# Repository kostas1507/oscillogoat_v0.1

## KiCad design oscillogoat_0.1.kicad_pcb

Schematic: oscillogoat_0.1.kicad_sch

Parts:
C1, C10, C13, C14, C15, C16, C17, C18, C19, C20, C21: 100u; 1206_3216Metric; MANUFACTURER PART NUMBER GRM31CR61A107MEA8
C2, C3, C5, C6, C7, C8, C11, C55, C56, C57, C58, C59, C60, C62, C63, C64, C66, C67, C68, C69, C70, C76, C77, C78, C80, C81, C83, C84, C86, C102, C112, C125, C126, C127, C138, C139, C140, C147, C163, C164, C165, C171, C172, C173, C187, C188, C192, C194, C196, C201, C202, C1038_1, C1043_1, C1044_1, C1045_1, C1046_1, C1047_1, C1048_1, C1049_1, C1050_1, C1052_1, C1053_1, C1054_1, C1055_1, C1056_1, C1057_1: 1uF; 0402_1005Metric; VOLTAGE RATING 25V; MANUFACTURER PART NUMBER GRM155R61E105KA12D
C4, C74, C174, C178, C190, C1034_1, C1035_1: 100pF; 0402_1005Metric; VOLTAGE RATING 50V; MANUFACTURER PART NUMBER GCM1555C1H101FA16D
C9, C12, C71, C72, C73, C85, C93, C94, C95, C96, C106, C111, C114, C115, C116, C117, C119, C120, C121, C122, C130, C131, C133, C142, C143, C144, C145, C146, C148, C149, C150, C151, C152, C153, C156, C166, C167, C169, C170, C175, C179, C181, C182, C183, C184, C186, C189, C203, C1003_1, C1004_1, C1005_1, C1006_1, C1007_1, C1007_2, C1007_3, C1008_1, C1008_2, C1040_1: 10uF; 0603_1608Metric; VOLTAGE RATING 25V; MANUFACTURER PART NUMBER GRM188R61E106MA73D
C75, C99, C101, C104, C105, C128, C176, C177, C180, C191: 22uF; 0805_2012Metric; VOLTAGE RATING 25V; MANUFACTURER PART NUMBER GRM21BR61E226ME44L
C82, C123, C124, C129, C132, C185, C1032_1, C1033_1, C1041_1, C1042_1: 100nF; 0402_1005Metric; VOLTAGE RATING 16V; MANUFACTURER PART NUMBER GCM155R71C104KA55D
C100: 12pF; 0402_1005Metric; VOLTAGE RATING 50V; MANUFACTURER PART NUMBER CBR04C120F5GAC
C154, C155, C168, C195: 47uF; 0805_2012Metric; VOLTAGE RATING 6.3V; MANUFACTURER PART NUMBER CL21A476MQYNNNE
C193, C197, C198, C199, C200: 100nF; 0402_1005Metric
C1002_1: 68pF; 0402_1005Metric; VOLTAGE RATING 50V; MANUFACTURER PART NUMBER GCM1555C1H680FA16J
C1030_1: 1nF; 0603_1608Metric; VOLTAGE RATING 100V; MANUFACTURER PART NUMBER GCM1885C2A102FA16D
F1, F2, F3, F4, F5, F6, F7, F8, F9, F10, F11: 120@100MHZ; 0402_1005Metric; MANUFACTURER PART NUMBER BLM15PX121SN1D
FB1001_1: 120@100MHZ; 0402_1005Metric; MANUFACTURER PART NUMBER BLM15PX121SN1D
IC1: XC7A12T-1CPG238C; BGA238C50P19X19_1000X1000X138; Mouser Part Number 217-XC7A12T-1CPG238C
IC2: FT601Q-B-T; QFN40P900X900X100-77N-D; Mouser Part Number 895-FT601Q-B-T
IC5: ADC09DJ800AAV; BGA144C80P12X12_1000X1000X194; Mouser Part Number 595-ADC09DJ800AAV
J1: 10137062-00021LF; 1013706200021LF; Manufacturer_Part_Number 10137062-00021LF
J5, J6: 2.54mm 6 Pin TH; GEN_2.54MM_6_PIN_TH_RA; MANUFACTURER PART NUMBER 61300611021
J1002_1: BNC; MOL_0731000105; MANUFACTURER PART NUMBER 73100-0105
L1, L2, L3, L5, L6: 1uH; 1210_3225Metric; MANUFACTURER PART NUMBER SRP3212-1R0M
Q1, Q2: DMN62D0UW; GEN_SOT_323; MANUFACTURER PART NUMBER DMN62D0UW-7
R1, R66, R67, R68, R72, R111, R117, R118, R121, R124, R131, R132, R1033_1, R1044_1: 10K; 0402_1005Metric; TOLERANCE 1%; MANUFACTURER PART NUMBER ERJ-2RKF1002X
R3: DNP; 0402_1005Metric; TOLERANCE 1%
R4, R6: DNP (place for LED); 0402_1005Metric; TOLERANCE 1%
R5: DNP (place for LED current limiter); 0402_1005Metric; TOLERANCE 1%
R7: 0; 0402_1005Metric; TOLERANCE 1%
R9, R10, R11, R12, R69, R99, R104, R112, R119, R136, R137, R138, R139, R140: 4.7K; 0402_1005Metric; TOLERANCE 1%; MANUFACTURER PART NUMBER ERJ-2RKF4701X
R13: 10K; GEN_R_2ARRAY_0606; TOLERANCE 1%; MANUFACTURER PART NUMBER ACASN1002S1002P1ATF1002X
R14, R57, R97, R98, R103, R116, R120, R123, R134: 0R01; 0603_1608Metric; TOLERANCE 1%; MANUFACTURER PART NUMBER RL0816T-R010-F
R15: 1K6R; 0402_1005Metric; TOLERANCE 1%
R16: 4K7R; 0402_1005Metric; TOLERANCE 1%
R17, R18: 10KR; 0402_1005Metric; TOLERANCE 1%
R52_1, R97_1: 0; 0402_1005Metric; MANUFACTURER PART NUMBER RC0402JR-070RL
R55, R96, R1041_1, R1042_1, R1047_1: 90.9k; 0402_1005Metric; TOLERANCE 1%; MANUFACTURER PART NUMBER RC0402FR-0790K9L
R56, R100, R105, R122: 20k; 0402_1005Metric; TOLERANCE 1%; MANUFACTURER PART NUMBER RC0402FR-0720KL
R70, R73: 5.1K; 0402_1005Metric; TOLERANCE 1%
R71: 3.75k; 0402_1005Metric; TOLERANCE 1%
R90, R106: 0.1; 0402_1005Metric; TOLERANCE 1%; MANUFACTURER PART NUMBER ERJ-2BSFR10X
R93, R109: 280K; 0402_1005Metric; TOLERANCE 1%; MANUFACTURER PART NUMBER AC0402FR-07280KL
R102: 3.4k; 0402_1005Metric; TOLERANCE 1%
R107, R143: 100; 0402_1005Metric; TOLERANCE 1%; MANUFACTURER PART NUMBER RC0402FR-07100RL
R110, R1036_1: 35.7k; 0402_1005Metric; TOLERANCE 1%; MANUFACTURER PART NUMBER RC0402FR-0735K7L
R113: 12.8k; 0402_1005Metric; TOLERANCE 1%
R125, R1045_1, R1046_1: 1K; 0402_1005Metric; TOLERANCE 1%; MANUFACTURER PART NUMBER RC0402FR-071KL
R127, R1043_1: 2K; 0402_1005Metric; TOLERANCE 1%; MANUFACTURER PART NUMBER RC0402FR-072KL
R141: 0R1; 0402_1005Metric; TOLERANCE 1%
R1003_1, R1038_1: 10M; 0603_1608Metric; TOLERANCE 1%; MANUFACTURER PART NUMBER RK73H1JTTD1005F
R1022_1, R1035_1: 30; 0603_1608Metric; TOLERANCE 1%; MANUFACTURER PART NUMBER SG73P1JTTD30R0F
R1037_1: 0; 0402_1005Metric; TOLERANCE 1%; MANUFACTURER PART NUMBER RC0402JR-070RL
R1039_1: 909k; 0402_1005Metric; TOLERANCE 1%; MANUFACTURER PART NUMBER RC0402FR-07909KL
R1048_1: DNP; 0402_1005Metric; TOLERANCE 1%; not fitted
R1049_1: 2K TRIMPOT; BOU_3mm_POT; TOLERANCE 1%; MANUFACTURER PART NUMBER TC33X-2-202E
S1: 416131160803
TP6, TP7, TP8, TP9, TP21, TP22, TP28, TP32, TP33, TP34, TP36, TP37, TP38, TP40, TP41, TP42, TP43, TP44, TP45, TP46, TP47, TP48, TP49, TP50, TP51, TP52, TP53, TP54, TP55, TP56, TP58, TP59, TP60, TP61, TP62, TP63, TP64, TP65, TP66, TP67, TP69, TP70, TP71, TP72, TP75, TP76, TP77, TP78, TP79, TP80, TP81, TP1017_1: PCB; GEN_TP_PCB
U2: MCP4452-104E; MC_TSSOP14; MANUFACTURER PART NUMBER MCP4452-104E
U3: MCP4728; MC_MSOP10_UN; MANUFACTURER PART NUMBER MCP4728T-E/UN
U4: REF2025; GEN_SOT23_5_950_2900X1600X1450; MANUFACTURER PART NUMBER REF2025AIDDCR
U5, U1011_1: OPA140AIDBVR; GEN_SOT23_5_950_2900X1600X1450; MANUFACTURER PART NUMBER OPA140AIDBVR
U8, U20, U21, U24: TPS62A02; TI_SOT563_DRL0006A; MANUFACTURER PART NUMBER TPS62A02DRLR
U13: LM27761; TI_WSON8_DSG0008A; MANUFACTURER PART NUMBER LM27761DSGR
U14, U15, U18, U22: TPS7A9101; TI_WSON10_DSK0010A; MANUFACTURER PART NUMBER TPS7A9101DSKR
U16: TPS7A2033; GEN_SOT23_5_950_2900X1600X1450; MANUFACTURER PART NUMBER TPS7A2033PDBVR
U17: TPS61023; TI_SOT563_DRL0006A; MANUFACTURER PART NUMBER TPS61023DRLT
U19: MX25L6433FZNI-08G; MX_WSON8; MANUFACTURER PART NUMBER MX25L6433FZNI-08G-TR
U1008_1: LMH6518; TI_WQFN_RGH0016A; MANUFACTURER PART NUMBER LMH6518SQX/NOPB
U1009_1: BUF802; TI_VQFN_RGT0016C; MANUFACTURER PART NUMBER BUF802IRGTR
Y1: ASEMPLV-100.000MHZ-LR-T; XTAL_ASEMPLV-100.000MHZ-LR-T; PARTREV 12.6.2018
Y2: 830107284409; Mouser Part Number 710-830107284409

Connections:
+1V0: C163.1, C164.1, C166.2, C167.2, C195.2, C196.1, F7.2, IC1.G10 (VCCINT_1), IC1.H10 (VCCINT_2), IC1.J10 (VCCINT_3), IC1.L10 (VCCINT_4), IC1.M10 (VCCINT_5), IC1.M11 (VCCBRAM_1), IC1.N10 (VCCINT_6), IC1.N11 (VCCBRAM_2), R116.2, TP66.1 (1_1)
+1V0_MGT: C17.1, C81.1, C83.1, F7.1, IC1.C1 (MGTAVCC_1), IC1.E1 (MGTAVCC_2), IC1.G9 (MGTAVCC_3), IC1.H9 (MGTAVCC_4)
+1V1_ACQ: C105.2, C133.2, C146.2, C149.2, C150.2, C152.2, F1.2, F2.2, F3.2, IC5.D8 (PLL_EN), R112.2, TP45.1 (1_1), U18.1 (OUT), U18.2 (OUT)
+1V2_MGT: C18.1, C84.1, C86.1, C183.2, C184.2, F8.1, F8.2, IC1.B1 (MGTAVTT_1), IC1.C5 (MGTAVTT_2), IC1.E2 (MGTAVTT_3), IC1.G7 (MGTAVTT_4), R125.1, R143.1, TP50.1 (1_1), U22.1 (OUT), U22.2 (OUT)
+1V8: C165.1, C168.2, C169.2, C170.2, C171.1, C172.1, C173.1, C186.2, C203.2, IC1.B19 (VCCO_15_1), IC1.C9 (VCCBATT_0), IC1.C14 (VCCO_15_2), IC1.C18 (VCCO_15_3), IC1.G13 (VCCO_15_4), IC1.H13 (VCCAUX_1), IC1.J13 (VCCAUX_2), R120.2, R123.1, R141.1, TP51.1 (1_1), TP64.1 (1_1)
+1V9_ACQ: C104.2, C117.2, C144.2, C145.2, C148.2, C151.2, F4.2, F5.2, F6.2, J6.1, R99.2, TP33.1 (1_1), U14.1 (OUT), U14.2 (OUT)
+2V2_AQ: R97.1, R134.2, TP36.1 (1_1), TP72.1 (1_1)
+2V5: R103.1, TP42.1 (1_1)
+3V3: C129.2, C138.1, C139.1, C140.1, C142.2, C143.2, C147.1, C154.2, C155.2, C156.2, C187.1, C188.1, C192.1, C201.1, C202.1, IC1.G12 (VCCO_0_1), IC1.K12 (VCCO_14_1), IC1.K13 (VCCO_14_2), IC1.L12 (VCCO_14_3), IC1.L13 (VCCO_14_4), IC1.M12 (VCCO_14_5), IC1.M13 (VCCO_14_6), IC1.N13 (VCCO_14_7), IC1.U12 (CFGBVS_0), IC1.V11 (VCCO_0_2), IC2.14 (VCCIO_1), IC2.20 (VCC33_1), IC2.24 (VCC33_2), IC2.28 (VDDA), IC2.38 (VCC33_3), IC2.49 (VCCIO_2), IC2.59 (VCCIO_3), IC2.68 (VCCIO_4), J5.6, R18.1, R57.2, R66.1, R67.2, R68.1, R136.2, R137.2, R138.2, R139.2, R140.2, TP70.1 (1_1), U19.8 (VCC), Y1.1 (TRI-STATE), Y1.6 (VDD)
+3V3_PGA: C76.1, C126.1, C1043_1.1, Q1.2 (G), Q2.2 (G), R9.2, R10.2, R1033_1.1, U16.5 (OUT), U1008_1.12 (VDD)
+5V: C2.1, C3.1, C5.1, C8.1, C85.2, C94.2, C95.2, C96.2, C121.2, C122.2, C1007_3.1, C1040_1.2, F9.1, F11.2, R11.2, R12.2, R100.2, R106.1, TP40.1 (1_1), U2.12 (VDD), U3.1 (VDD), U4.3 (EN), U4.4 (VIN), U5.5 (V+), U15.1 (OUT), U15.2 (OUT)
+5V3: C100.2, C101.2, C102.1, C128.2, R90.1, R98.1, R109.2, TP37.1 (1_1), TP41.1 (1_1), U17.6 (VOUT)
+5V_BUF: C21.1, C1004_1.2, C1006_1.2, C1008_1.2, C1044_1.1, C1045_1.1, C1046_1.1, C1047_1.1, C1048_1.1, C1049_1.1, C1050_1.1, F11.1, U1009_1.1 (Vs+), U1009_1.12 (Vso+), U1009_1.15 (CLH), U1011_1.5 (V+)
+5V_PGA: C19.1, C1008_2.2, C1038_1.1, F9.2, U1008_1.3 (VCC), U1008_1.4 (VCC)
+VBIAS: C6.1, C1033_1.2, R13.2, R1045_1.1, R1046_1.1, TP8.1 (1_1), U4.5 (VREF)
+VUSB: C9.2, C12.2, C71.2, C72.2, C73.2, C175.2, C179.2, C189.2, J1.A4 (VBUS_1), J1.A9 (VBUS_2), J1.B4 (VBUS_3), J1.B9 (VBUS_4), R1.2, R14.1, R16.2, R117.2, R121.2, R131.2, TP21.1 (1_1), U8.3 (VIN), U20.3 (VIN), U21.3 (VIN), U24.3 (VIN)
-5V: C11.2, C93.1, C106.2, C1007_2.1, F10.1, R93.2, U5.2 (V-), U13.4 (VOUT)
-5V_BUF: C20.1, C1003_1.1, C1005_1.1, C1007_1.1, C1052_1.2, C1053_1.2, C1054_1.2, C1055_1.2, C1056_1.2, C1057_1.2, F10.2, R1036_1.2, U1009_1.5 (Vs-), U1009_1.6 (Aux_Bias), U1009_1.8 (Vs-), U1009_1.10 (Vso-), U1011_1.2 (V-)
-VBIAS: C82.2, C1032_1.2, R107.1, R1042_1.1, TP9.1 (1_1)
/1V9_AQ_PG: U14.5 (PG), U18.7 (EN)
/+1V0_R: C174.2, C176.2, C177.2, L2.2, R69.2, R116.1, R118.2, TP65.1 (1_1)
/+1V8_R: C178.2, C180.2, L3.2, R120.1, R122.2, TP63.1 (1_1)
/+1V8_R_LDO: C181.2, C182.2, R123.2, TP49.1 (1_1), U22.6 (SS_CTRL), U22.9 (IN), U22.10 (IN)
/+2V5_R: C190.2, C191.2, L6.2, R132.2, R134.1, TP71.1 (1_1)
/+2V5_R_ACQ: C115.2, C116.2, C130.2, C131.2, R97.2, R103.2, TP32.1 (1_1), TP44.1 (1_1), U14.6 (SS_CTRL), U14.9 (IN), U14.10 (IN), U18.6 (SS_CTRL), U18.9 (IN), U18.10 (IN)
/+3V3_R: C74.2, C75.2, L5.2, R55.1, R57.1, TP69.1 (1_1)
/+5V3_R_CP: C111.2, R90.2, TP28.1 (1_1), U13.1 (VIN)
/+5V3_R_LDO: C119.2, C120.2, R98.2, TP34.1 (1_1), U15.9 (IN), U15.10 (IN)
/+5V_R_PGA: C125.1, R106.2, TP38.1 (1_1), U16.1 (IN), U16.3 (EN)
/+VUSB_R: C99.2, C127.1, L1.1, R14.2, R72.2, TP22.1 (1_1), U17.3 (VIN)
/ADC_DEVCLK_N: IC5.G1 (CLK-), Y1.5 (~OUTPUT)
/ADC_DEVCLK_P: IC5.F1 (CLK+), Y1.4 (OUTPUT)
/ADC_INA+: IC5.A2 (INA+)
/ADC_INA-: IC5.A3 (INA-)
/ADC_JESD_0_N: IC1.A4 (MGTPRXN0_216), IC5.K12 (D0-)
/ADC_JESD_0_P: IC1.B4 (MGTPRXP0_216), IC5.J12 (D0+)
/ADC_JESD_1_N: IC1.A6 (MGTPRXN1_216), IC5.H12 (D1-)
/ADC_JESD_1_P: IC1.B6 (MGTPRXP1_216), IC5.G12 (D1+)
/ADC_SPI_CLK: IC1.A17 (IO_L6N_T0_VREF_15), IC5.F8 (SCLK), J6.2
/ADC_SPI_SCS: IC1.A15 (IO_L10N_T1_AD4N_15), IC5.E8 (~SCS), J6.3
/ADC_SPI_SDI: IC1.A14 (IO_L10P_T1_AD4P_15), IC5.G8 (SDI), J6.4
/ADC_SPI_SDO: IC1.A16 (IO_L11N_T1_SRCC_AD12N_15), IC5.G9 (SDO), J6.5
/ATTEN_OUT: R1022_1.1, R1035_1.1, R1039_1.1
/ATTEN_OUT_R: C1030_1.2, R1035_1.2
/BE_0: IC1.R17 (IO_L17N_T2_A13_D29_14), IC2.4 (BE_0)
/BE_1: IC1.T17 (IO_L18P_T2_A12_D28_14), IC2.5 (BE_1)
/BE_2: IC1.P17 (IO_L17P_T2_A14_D30_14), IC2.6 (BE_2)
/BE_3: IC1.N17 (IO_L14P_T2_SRCC_14), IC2.7 (BE_3)
/BUF_IN: C1030_1.1, R1038_1.2, U1009_1.2 (IN)
/BUF_IN_AUX: C1034_1.2, R1043_1.1, U1009_1.4 (IN_Aux)
/BUF_IN_BIAS: R1038_1.1, U1009_1.3 (IN_Bias)
/BUF_OUT: R1037_1.1, R1041_1.1, U1009_1.11 (OUT)
/BUF_OUT_R: R1037_1.2, U1008_1.6 (IN_P)
/BUF_R_BIAS: R1036_1.1, U1009_1.7 (R_Bias)
/DC_FB: C1002_1.2, C1035_1.2, R1041_1.2, R1042_1.2, R1044_1.1, U1011_1.4 (-)
/DC_FB_TRIM: R1044_1.2, R1048_1.2, R1049_1.1, R1049_1.2
/DN: IC2.25 (DM), J1.A7 (DN1), J1.B7 (DN2)
/DONE: IC1.U11 (DONE_0), R3.2
/DP: IC2.23 (DP), J1.A6 (DP1), J1.B6 (DP2)
/FE_EN: R111.1, U13.6 (EN), U15.7 (EN)
/FE_PG: U15.5 (PG)
/FPGA_EN: R117.1, TP81.1 (1_1), U20.4 (EN)
/FTDI_XI: C199.2, IC2.21 (XI), Y2.3 (CRYSTAL_2)
/FTDI_XO: C200.1, IC2.22 (XO), Y2.1 (CRYSTAL_1)
/M0: IC1.V13 (M0_0), R140.1, S1.A3
/M1: IC1.W13 (M1_0), R139.1, S1.A2
/M2: IC1.U13 (M2_0), R138.1, S1.A1
/OE_N: IC1.U17 (IO_L19P_T3_A10_D26_14), IC2.13 (OE_N)
/OPA_OUT: C1002_1.1, C1035_1.1, R1043_1.2, U1011_1.1 (OUT)
/OUT_N: R97_1.2
/OUT_P: R52_1.2
/OUT_R_N: R97_1.1, U1008_1.14 (OUT_N)
/OUT_R_P: R52_1.1, U1008_1.15 (OUT_P)
/PGA_BIAS: C1042_1.2, FB1001_1.2, R1045_1.2, R1046_1.2, TP1017_1.1 (1_1), U1008_1.7 (IN_N)
/PGA_CSn: R1033_1.2, U1008_1.9 (CSn)
/PGA_SCLK: U1008_1.11 (SCLK)
/PGA_SDIO: U1008_1.10 (SDIO)
/PG_1V0: R121.1, TP79.1 (1_1), U20.6 (PG), U21.4 (EN)
/PG_1V8: R1.1, R131.1, TP80.1 (1_1), U8.4 (EN), U21.6 (PG), U22.7 (EN), U24.4 (EN)
/QSPI_CLK: IC1.C11 (CCLK_0), TP43.1 (1_1), U19.6 (SCLK)
/QSPI_CS: IC1.G19 (IO_L6P_T0_FCS_B_14), R67.1, TP53.1 (1_1), U19.1 (CS#)
/QSPI_DQ0: IC1.D18 (IO_L1P_T0_D00_MOSI_14), TP47.1 (1_1), U19.5 (SI/SIO0)
/QSPI_DQ1: IC1.D19 (IO_L1N_T0_D01_DIN_14), TP46.1 (1_1), U19.2 (SO/SIO1)
/QSPI_DQ2: IC1.E19 (IO_L2P_T0_D02_14), R66.2, TP48.1 (1_1), U19.3 (WP#/SIO2)
/QSPI_DQ3: IC1.F19 (IO_L2N_T0_D03_14), R68.2, TP52.1 (1_1), U19.7 (HOLD#/SIO3)
/RD_N: IC1.U16 (IO_L22N_T3_A04_D20_14), IC2.12 (RD_N)
/RXF_N: IC1.V16 (IO_L21P_T3_DQS_14), IC2.9 (RXF_N)
/SIWU_N: IC1.V14 (IO_L23P_T3_A03_D19_14), IC2.10 (SIWU_N)
/SSRXN: IC2.34 (RIDN), J1.A10 (SSRXN2)
/SSRXP: IC2.35 (RIDP), J1.A11 (SSRXP2)
/SSTXN: C193.1, J1.A3 (SSTXN1)
/SSTXP: C197.1, J1.A2 (SSTXP1)
/TCK: IC1.C8 (TCK_0), J5.4, TP77.1 (1_1)
/TDI: IC1.W11 (TDI_0), J5.2, TP75.1 (1_1)
/TDO: IC1.V10 (TDO_0), J5.3, TP76.1 (1_1)
/TMS: IC1.W10 (TMS_0), J5.1, TP78.1 (1_1)
/TRIM_1: C1041_1.2, FB1001_1.1, U2.14 (P2W)
/TRIM_2: U2.9 (P0W)
/TRIM_3: U2.8 (P1W)
/TRIM_4: U2.1 (P3W)
/TRIM_SCL: Q1.3 (S), R9.1, TP59.1 (1_1)
/TRIM_SCL_5V: Q1.1 (D), R11.1, TP6.1 (1_1), U2.4 (SCL), U3.2 (SCL)
/TRIM_SDA: Q2.3 (S), R10.1, TP60.1 (1_1)
/TRIM_SDA_5V: Q2.1 (D), R12.1, TP7.1 (1_1), U2.5 (SDA), U3.3 (SDA)
/TXE_N: IC1.U15 (IO_L22P_T3_A05_D21_14), IC2.8 (TXE_N)
/U5-: C4.1, R13.1, R13.3, U5.4 (-)
/VCM: U1008_1.13 (VCM)
/VOUT1: U2.13 (P2B), U3.6 (VOUTA)
/VOUT2: U2.10 (P0B), U3.7 (VOUTB)
/VOUT3: U2.7 (P1B), U3.8 (VOUTC)
/VOUT4: U2.2 (P3B), U3.9 (VOUTD)
/WR_N: IC1.U14 (IO_25_14), IC2.11 (WR_N)
/p0: IC1.G17 (IO_L5N_T0_D07_14), IC2.40 (DATA_0)
/p1: IC1.F17 (IO_L5P_T0_D06_14), IC2.41 (DATA_1)
/p2: IC1.E17 (IO_L3P_T0_DQS_PUDC_B_14), IC2.42 (DATA_2)
/p3: IC1.D17 (IO_0_14), IC2.43 (DATA_3)
/p4: IC1.M17 (IO_L10P_T1_D14_14), IC2.44 (DATA_4)
/p5: IC1.L17 (IO_L12N_T1_MRCC_14), IC2.45 (DATA_5)
/p6: IC1.K17 (IO_L12P_T1_MRCC_14), IC2.46 (DATA_6)
/p7: IC1.J17 (IO_L7N_T1_D10_14), IC2.47 (DATA_7)
/p8: IC1.H17 (IO_L7P_T1_D09_14), IC2.50 (DATA_8)
/p9: IC1.E18 (IO_L3N_T0_DQS_EMCCLK_14), IC2.51 (DATA_9)
/p10: IC1.G18 (IO_L4P_T0_D04_14), IC2.52 (DATA_10)
/p11: IC1.H18 (IO_L4N_T0_D05_14), IC2.53 (DATA_11)
/p12: IC1.K18 (IO_L11P_T1_SRCC_14), IC2.54 (DATA_12)
/p13: IC1.H19 (IO_L6N_T0_D08_VREF_14), IC2.55 (DATA_13)
/p14: IC1.J19 (IO_L8P_T1_D11_14), IC2.56 (DATA_14)
/p15: IC1.K19 (IO_L8N_T1_D12_14), IC2.57 (DATA_15)
/p16: IC1.L18 (IO_L11N_T1_SRCC_14), IC2.60 (DATA_16)
/p17: IC1.N18 (IO_L10N_T1_D15_14), IC2.61 (DATA_17)
/p18: IC1.P18 (IO_L14N_T2_SRCC_14), IC2.62 (DATA_18)
/p19: IC1.T18 (IO_L18N_T2_A11_D27_14), IC2.63 (DATA_19)
/p20: IC1.M19 (IO_L9N_T1_DQS_D13_14), IC2.64 (DATA_20)
/p21: IC1.N19 (IO_L13P_T2_MRCC_14), IC2.65 (DATA_21)
/p22: IC1.P19 (IO_L13N_T2_MRCC_14), IC2.66 (DATA_22)
/p23: IC1.R19 (IO_L15P_T2_DQS_RDWR_B_14), IC2.67 (DATA_23)
/p24: IC1.T19 (IO_L15N_T2_DQS_DOUT_CSO_B_14), IC2.69 (DATA_24)
/p25: IC1.U19 (IO_L16P_T2_CSI_B_14), IC2.70 (DATA_25)
/p26: IC1.V19 (IO_L16N_T2_A15_D31_14), IC2.71 (DATA_26)
/p27: IC1.W18 (IO_L20N_T3_A07_D23_14), IC2.72 (DATA_27)
/p28: IC1.W17 (IO_L20P_T3_A08_D24_14), IC2.73 (DATA_28)
/p29: IC1.W16 (IO_L24N_T3_A00_D16_14), IC2.74 (DATA_29)
/p30: IC1.W15 (IO_L24P_T3_A01_D17_14), IC2.75 (DATA_30)
/p31: IC2.76 (DATA_31), R7.1
/p31_FPGA: IC1.W14 (IO_L23N_T3_A02_D18_14), R5.2, R7.2
/p_CLK: IC1.L19 (IO_L9P_T1_DQS_14), IC2.58 (CLK)
GND: C1.2, C2.2, C3.2, C5.2, C6.2, C7.2, C8.2, C9.1, C10.2, C11.1, C12.1, C13.2, C14.2, C15.2, C16.2, C17.2, C18.2, C19.2, C20.2, C21.2, C55.2, C56.2, C57.2, C58.2, C59.2, C60.2, C62.2, C63.2, C64.2, C66.2, C67.2, C68.2, C69.2, C70.2, C71.1, C72.1, C73.1, C75.1, C76.2, C77.2, C78.2, C80.2, C81.2, C82.1, C83.2, C84.2, C85.1, C86.2, C93.2, C94.1, C95.1, C96.1, C99.1, C101.1, C102.2, C104.1, C105.1, C106.1, C111.1, C114.1, C115.1, C116.1, C117.1, C119.1, C120.1, C121.1, C122.1, C123.1, C124.1, C125.2, C126.2, C127.2, C128.1, C129.1, C130.1, C131.1, C132.1, C133.1, C138.2, C139.2, C140.2, C142.1, C143.1, C144.1, C145.1, C146.1, C147.2, C148.1, C149.1, C150.1, C151.1, C152.1, C153.1, C154.1, C155.1, C156.1, C163.2, C164.2, C165.2, C166.1, C167.1, C168.1, C169.1, C170.1, C171.2, C172.2, C173.2, C175.1, C176.1, C177.1, C179.1, C180.1, C181.1, C182.1, C183.1, C184.1, C185.1, C186.1, C187.2, C188.2, C189.1, C191.1, C192.2, C194.2, C195.1, C196.2, C198.1, C199.1, C200.2, C201.2, C202.2, C203.1, C1003_1.2, C1004_1.1, C1005_1.2, C1006_1.1, C1007_1.2, C1007_2.2, C1007_3.2, C1008_1.1, C1008_2.1, C1032_1.1, C1033_1.1, C1034_1.1, C1038_1.2, C1040_1.1, C1041_1.1, C1042_1.1, C1043_1.2, C1044_1.2, C1045_1.2, C1046_1.2, C1047_1.2, C1048_1.2, C1049_1.2, C1050_1.2, C1052_1.1, C1053_1.1, C1054_1.1, C1055_1.1, C1056_1.1, C1057_1.1, IC1.A1 (GND_1), IC1.A3 (GND_2), IC1.A5 (GND_3), IC1.A7 (GND_4), IC1.A9 (GND_5), IC1.A11 (DXP_0), IC1.A12 (VP_0), IC1.A13 (VREFN_0), IC1.A19 (GND_6), IC1.B3 (GND_7), IC1.B5 (GND_8), IC1.B7 (GND_9), IC1.B9 (GND_10), IC1.B11 (DXN_0), IC1.B12 (VREFP_0), IC1.B13 (VN_0), IC1.B14 (GND_11), IC1.C2 (GND_12), IC1.C3 (GND_13), IC1.C4 (GND_14), IC1.C6 (GND_15), IC1.C10 (GND_16), IC1.C12 (GNDADC_0), IC1.C19 (GND_17), IC1.D3 (GND_18), IC1.E3 (GND_19), IC1.F1 (GND_20), IC1.F2 (GND_21), IC1.F3 (GND_22), IC1.F18 (GND_23), IC1.G8 (GND_24), IC1.G11 (GND_25), IC1.H7 (GND_26), IC1.H8 (GND_27), IC1.H11 (GND_28), IC1.H12 (GND_29), IC1.J2 (GND_30), IC1.J7 (VCCO_34_1), IC1.J8 (GND_31), IC1.J9 (GND_32), IC1.J11 (GND_33), IC1.J12 (GND_34), IC1.J18 (GND_35), IC1.K7 (VCCO_34_2), IC1.K8 (GND_36), IC1.L7 (VCCO_34_3), IC1.L8 (GND_37), IC1.L9 (GND_38), IC1.L11 (GND_39), IC1.M2 (GND_40), IC1.M7 (VCCO_34_4), IC1.M8 (VCCO_34_5), IC1.M9 (GND_41), IC1.M18 (GND_42), IC1.N7 (VCCO_34_6), IC1.N8 (VCCO_34_7), IC1.N9 (GND_43), IC1.N12 (GND_44), IC1.R2 (GND_45), IC1.R18 (GND_46), IC1.V2 (GND_47), IC1.V5 (GND_48), IC1.V8 (GND_49), IC1.V12 (GND_50), IC1.V15 (GND_51), IC1.V18 (GND_52), IC1.W1 (GND_53), IC1.W19 (GND_54), IC2.1 (GND_1), IC2.26 (GND_2), IC2.29 (GND_3), IC2.36 (GND_4), IC2.77 (THERMAL_PAD), IC5.A1 (AGND_1), IC5.A4 (AGND_2), IC5.A5 (AGND_3), IC5.A8 (AGND_4), IC5.A11 (DGND_1), IC5.A12 (DGND_2), IC5.B1 (AGND_5), IC5.B2 (AGND_6), IC5.B3 (AGND_7), IC5.B4 (AGND_8), IC5.B5 (AGND_9), IC5.B6 (AGND_10), IC5.B7 (AGND_11), IC5.B8 (AGND_12), IC5.B11 (DGND_3), IC5.B12 (DGND_4), IC5.C2 (AGND_13), IC5.C4 (~SYNCSE), IC5.C5 (AGND_14), IC5.C6 (AGND_15), IC5.C7 (CLKCFG0), IC5.C8 (PLLREF_SE), IC5.C10 (DGND_5), IC5.D2 (AGND_16), IC5.D3 (AGND_17), IC5.D7 (CLKCFG1), IC5.E1 (AGND_18), IC5.E2 (AGND_19), IC5.E4 (AGND_20), IC5.E7 (AGND_21), IC5.F2 (SE_CLK), IC5.F4 (AGND_22), IC5.F7 (AGND_23), IC5.F10 (DGND_6), IC5.G2 (SE_GND), IC5.G4 (AGND_24), IC5.G7 (AGND_25), IC5.G10 (DGND_7), IC5.H1 (AGND_26), IC5.H2 (AGND_27), IC5.H4 (AGND_28), IC5.H7 (AGND_29), IC5.J2 (AGND_30), IC5.J3 (PGND_1), IC5.K2 (AGND_31), IC5.K5 (PGND_2), IC5.K10 (DGND_8), IC5.L1 (AGND_32), IC5.L2 (AGND_33), IC5.L3 (AGND_34), IC5.L4 (AGND_35), IC5.L5 (AGND_36), IC5.L6 (AGND_37), IC5.L7 (AGND_38), IC5.L8 (AGND_39), IC5.L9 (DGND_9), IC5.L11 (DGND_10), IC5.L12 (DGND_11), IC5.M1 (AGND_40), IC5.M4 (AGND_41), IC5.M5 (AGND_42), IC5.M8 (AGND_43), IC5.M9 (PD), IC5.M11 (DGND_12), IC5.M12 (DGND_13), J1.A1 (GND_1), J1.A12 (GND_2), J1.B1 (GND_3), J1.B12 (GND_4), J1.MH3 (MH4), J1.MH4 (MH1), J1.MH5 (MH3), J1.MH6 (MH2), J5.5, J6.6, J1002_1.2 (SHIELD), R4.1, R6.1, R15.1, R17.1, R56.1, R70.1, R71.1, R73.2, R96.1, R102.1, R104.1, R105.1, R110.2, R111.2, R113.1, R119.2, R124.1, R127.2, R1003_1.2, R1047_1.2, R1048_1.1, R1049_1.3, S1.1, S1.2, S1.3, U2.3 (HVC/A0), U2.6 (VSS), U2.11 (A1), U3.4 (LDACn), U3.10 (VSS), U4.2 (GND), U5.3 (+), U8.1 (GND), U13.2 (GND), U13.9 (PAD), U14.4 (GND), U14.11 (PAD), U15.4 (GND), U15.6 (SS_CTRL), U15.11 (PAD), U16.2 (GND), U17.4 (GND), U18.4 (GND), U18.11 (PAD), U19.4 (GND), U19.9 (PAD), U20.1 (GND), U21.1 (GND), U22.4 (GND), U22.11 (PAD), U24.1 (GND), U1008_1.5 (GND), U1008_1.8 (GND), U1008_1.17 (PAD), U1009_1.14 (CLL), U1009_1.17 (PAD), Y1.3 (GND), Y2.2 (GND_1), Y2.4 (GND_2)
unnamed: IC1.W12 (INIT_B_0), R137.1
unnamed: IC1.U10 (PROGRAM_B_0), R136.1
unnamed: IC1.C7 (MGTRREF_216), R143.2
unnamed: C194.1, IC1.C13 (VCCADC_0), R141.2
unnamed: C153.2, IC2.2 (AVDD), IC2.3 (VD10_1), IC2.30 (VD10_2), IC2.33 (VD10_3), IC2.39 (DV10), IC2.48 (VD10_4)
unnamed: IC2.37 (VBUS), R16.1, R17.2
unnamed: IC2.17 (GPIO0), TP61.1 (1_1)
unnamed: IC2.18 (GPIO1), TP62.1 (1_1)
unnamed: C198.2, IC2.15 (RESET_N), R18.2, TP67.1 (1_1)
unnamed: IC2.27 (RREF), R15.2
unnamed: C193.2, IC2.31 (TODN)
unnamed: C197.2, IC2.32 (TODP)
unnamed: IC2.16 (WAKEUP_N), TP58.1 (1_1)
unnamed: IC5.C3 (BG), TP54.1 (1_1)
unnamed: IC5.B9 (CALSTAT), TP55.1 (1_1)
unnamed: IC5.C9 (ORA), TP56.1 (1_1)
unnamed: C13.1, C63.1, C64.1, C66.1, C67.1, F3.1, IC5.D6 (VA11_1), IC5.E3 (VA11_2), IC5.E5 (VA11_3), IC5.F3 (VA11_4), IC5.F5 (VA11_5), IC5.G3 (VA11_6), IC5.G5 (VA11_7), IC5.H3 (VA11_8), IC5.H5 (VA11_9), IC5.J6 (VA11_10)
unnamed: C14.1, C57.1, C58.1, C59.1, C60.1, F4.1, IC5.D4 (VA19_1), IC5.D5 (VA19_2), IC5.E6 (VA19_3), IC5.F6 (VA19_4), IC5.G6 (VA19_5), IC5.H6 (VA19_6)
unnamed: C10.1, C68.1, C69.1, C70.1, C77.1, C78.1, F2.1, IC5.A10 (VD11_1), IC5.B10 (VD11_2), IC5.D10 (VD11_3), IC5.E10 (VD11_4), IC5.H8 (VD11_5), IC5.H9 (VD11_6), IC5.H10 (VD11_7), IC5.J10 (VD11_8), IC5.L10 (VD11_9), IC5.M10 (VD11_10)
unnamed: C16.1, C55.1, C56.1, F6.1, IC5.J4 (VPLL19_1), IC5.J5 (VPLL19_2)
unnamed: C15.1, C62.1, F5.1, IC5.K6 (VREFO)
unnamed: C1.1, C80.1, F1.1, IC5.J8 (VTRIG_1), IC5.K8 (VTRIG_2)
unnamed: J1.A5 (CC1), R70.2
unnamed: J1.B5 (CC2), R73.1
unnamed: J1002_1.1 (Signal), R1022_1.2
unnamed: R3.1, R4.2
unnamed: R5.1, R6.2
unnamed: C7.1, U4.1 (VBIAS)
unnamed: C4.2, R13.4, R107.2, U5.1 (OUT)
unnamed: C74.1, R55.2, R56.2, U8.5 (FB)
unnamed: L5.1, U8.2 (SW)
unnamed: C112.1, U13.8 (C1+)
unnamed: C112.2, U13.7 (C1-)
unnamed: C114.2, U13.3 (CPOUT)
unnamed: R93.1, R96.2, U13.5 (VFB)
unnamed: R99.1, R102.2, U14.3 (FB)
unnamed: C123.2, U14.8 (NR/SS)
unnamed: R100.1, R104.2, R105.2, U15.3 (FB)
unnamed: C124.2, U15.8 (NR/SS)
unnamed: R72.1, U17.2 (EN)
unnamed: C100.1, R109.1, R110.1, U17.1 (FB)
unnamed: L1.2, U17.5 (SW)
unnamed: R112.1, R113.2, U18.3 (FB)
unnamed: C132.2, U18.8 (NR/SS)
unnamed: C174.1, R69.1, R118.1, R119.1, U20.5 (FB)
unnamed: L2.1, U20.2 (SW)
unnamed: C178.1, R122.1, R124.2, U21.5 (FB)
unnamed: L3.1, U21.2 (SW)
unnamed: R125.2, R127.1, U22.3 (FB)
unnamed: C185.2, U22.8 (NR/SS)
unnamed: C190.1, R71.2, R132.1, U24.5 (FB)
unnamed: L6.1, U24.2 (SW)
unnamed: R1003_1.1, R1039_1.2, R1047_1.1, U1011_1.3 (+)

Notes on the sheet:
Vout = 0.6 * (R1/R2 + 1)
FPGA TRANSCEIVERS
1V,1V,1.2V
Bias Voltage Generation
1.2/1.8 = 66.7% efficiency
Default I2C address: 1100000
DONE: Use 100kOhm digipot
85% measured efficiency
Offset Voltage Trim and User Offset Control
Vout = 0.6 * (10/3.75 + 1)
The value for R2 must be no less than 50 kΩ.
5V: 68.4mA, 70.6mA measured
The recommended power-on sequence to achieve minimum current draw for the GTP transceivers is VCCINT, VMGTAVCC, VMGTAVTT
Vout = 0.8 * (20/3.8 +1)
FPGA CONF
Tss = (0.8 × 100nF) / 6.2uA [for SS_CTRL = GND]
Vout = 0.6 * (90.9/20 + 1)
Vout = 1.094V
Tss = (VREF × Cnr/ss) / Inr/ss
ADC & ADC POWER
USB
Vout = 0.8 * (R1/R2 +1)
Vout = 0.8 * (1/2 +1)
Vout = 3.327V
Default I2C address: 0101100
Vout = -1.22V*(R1+R2)/R2
5V3: 79.4mA measured
Vout = (280/35.7+1)*0.6 = 5.31V
Tss = 0.0129s = 13ms
VBIAS Pin is 1/2 of 2.5V VREF
Vout = -1.22*(280/90.9+1)= -4.98V
Vout = 1.905V
Max current for 35.7kOhm R_Bias: 24mA @ V+ and 24mA @ V-
Vout = 1.2V
Use VREF For OUR +VBIAS
Vout = 0.6 * (3.197/4.7 + 1)
Vout = 5.01V
Vout = 2.2V
5V: 968mA pre-config
Vout = 0.6 * (20/10 + 1)

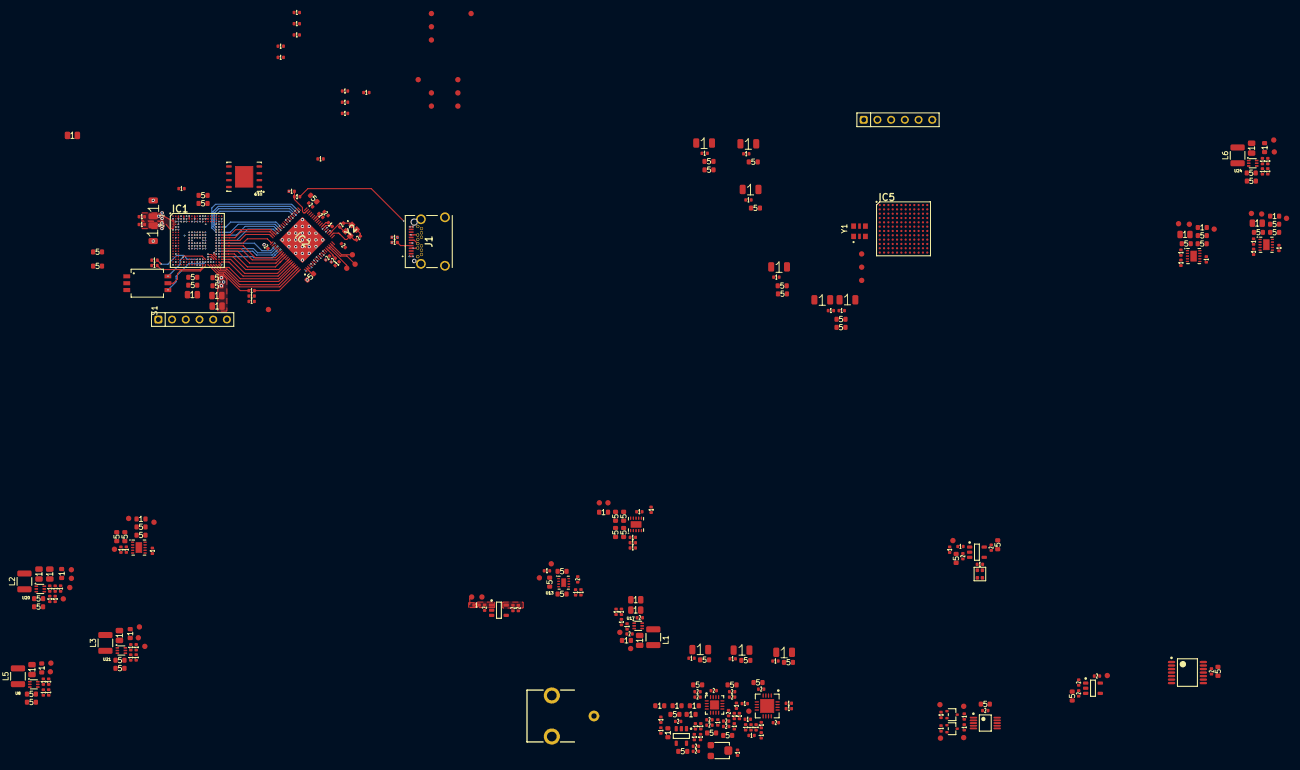
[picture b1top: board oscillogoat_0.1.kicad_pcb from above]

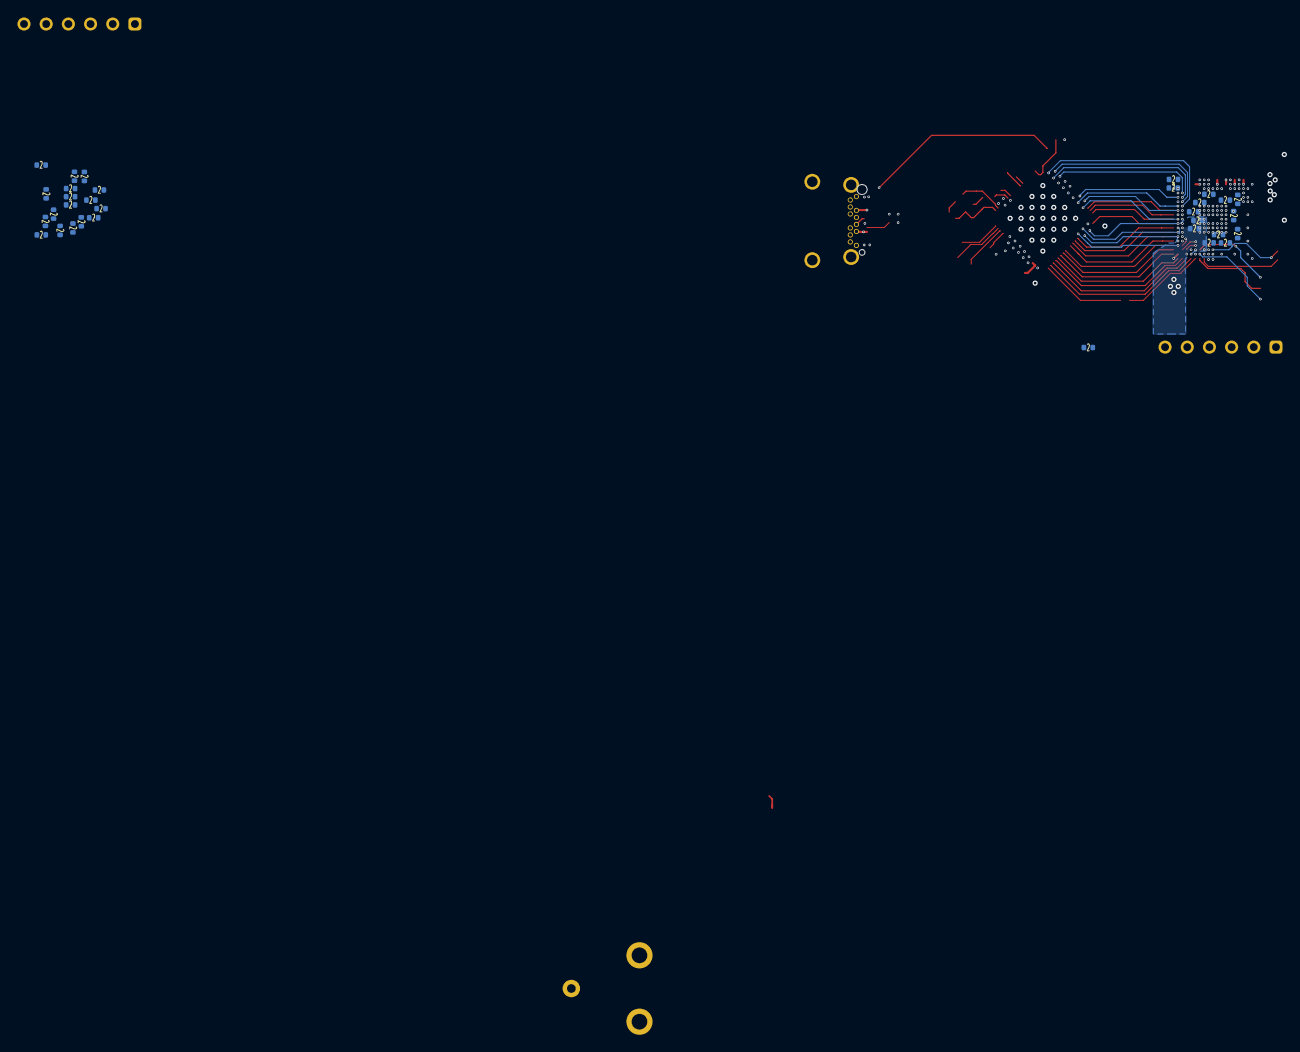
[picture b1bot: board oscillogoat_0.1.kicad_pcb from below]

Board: 6 copper layers, 359 parts (32 on the bottom side), 189 nets.

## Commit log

2026-03-19 init
